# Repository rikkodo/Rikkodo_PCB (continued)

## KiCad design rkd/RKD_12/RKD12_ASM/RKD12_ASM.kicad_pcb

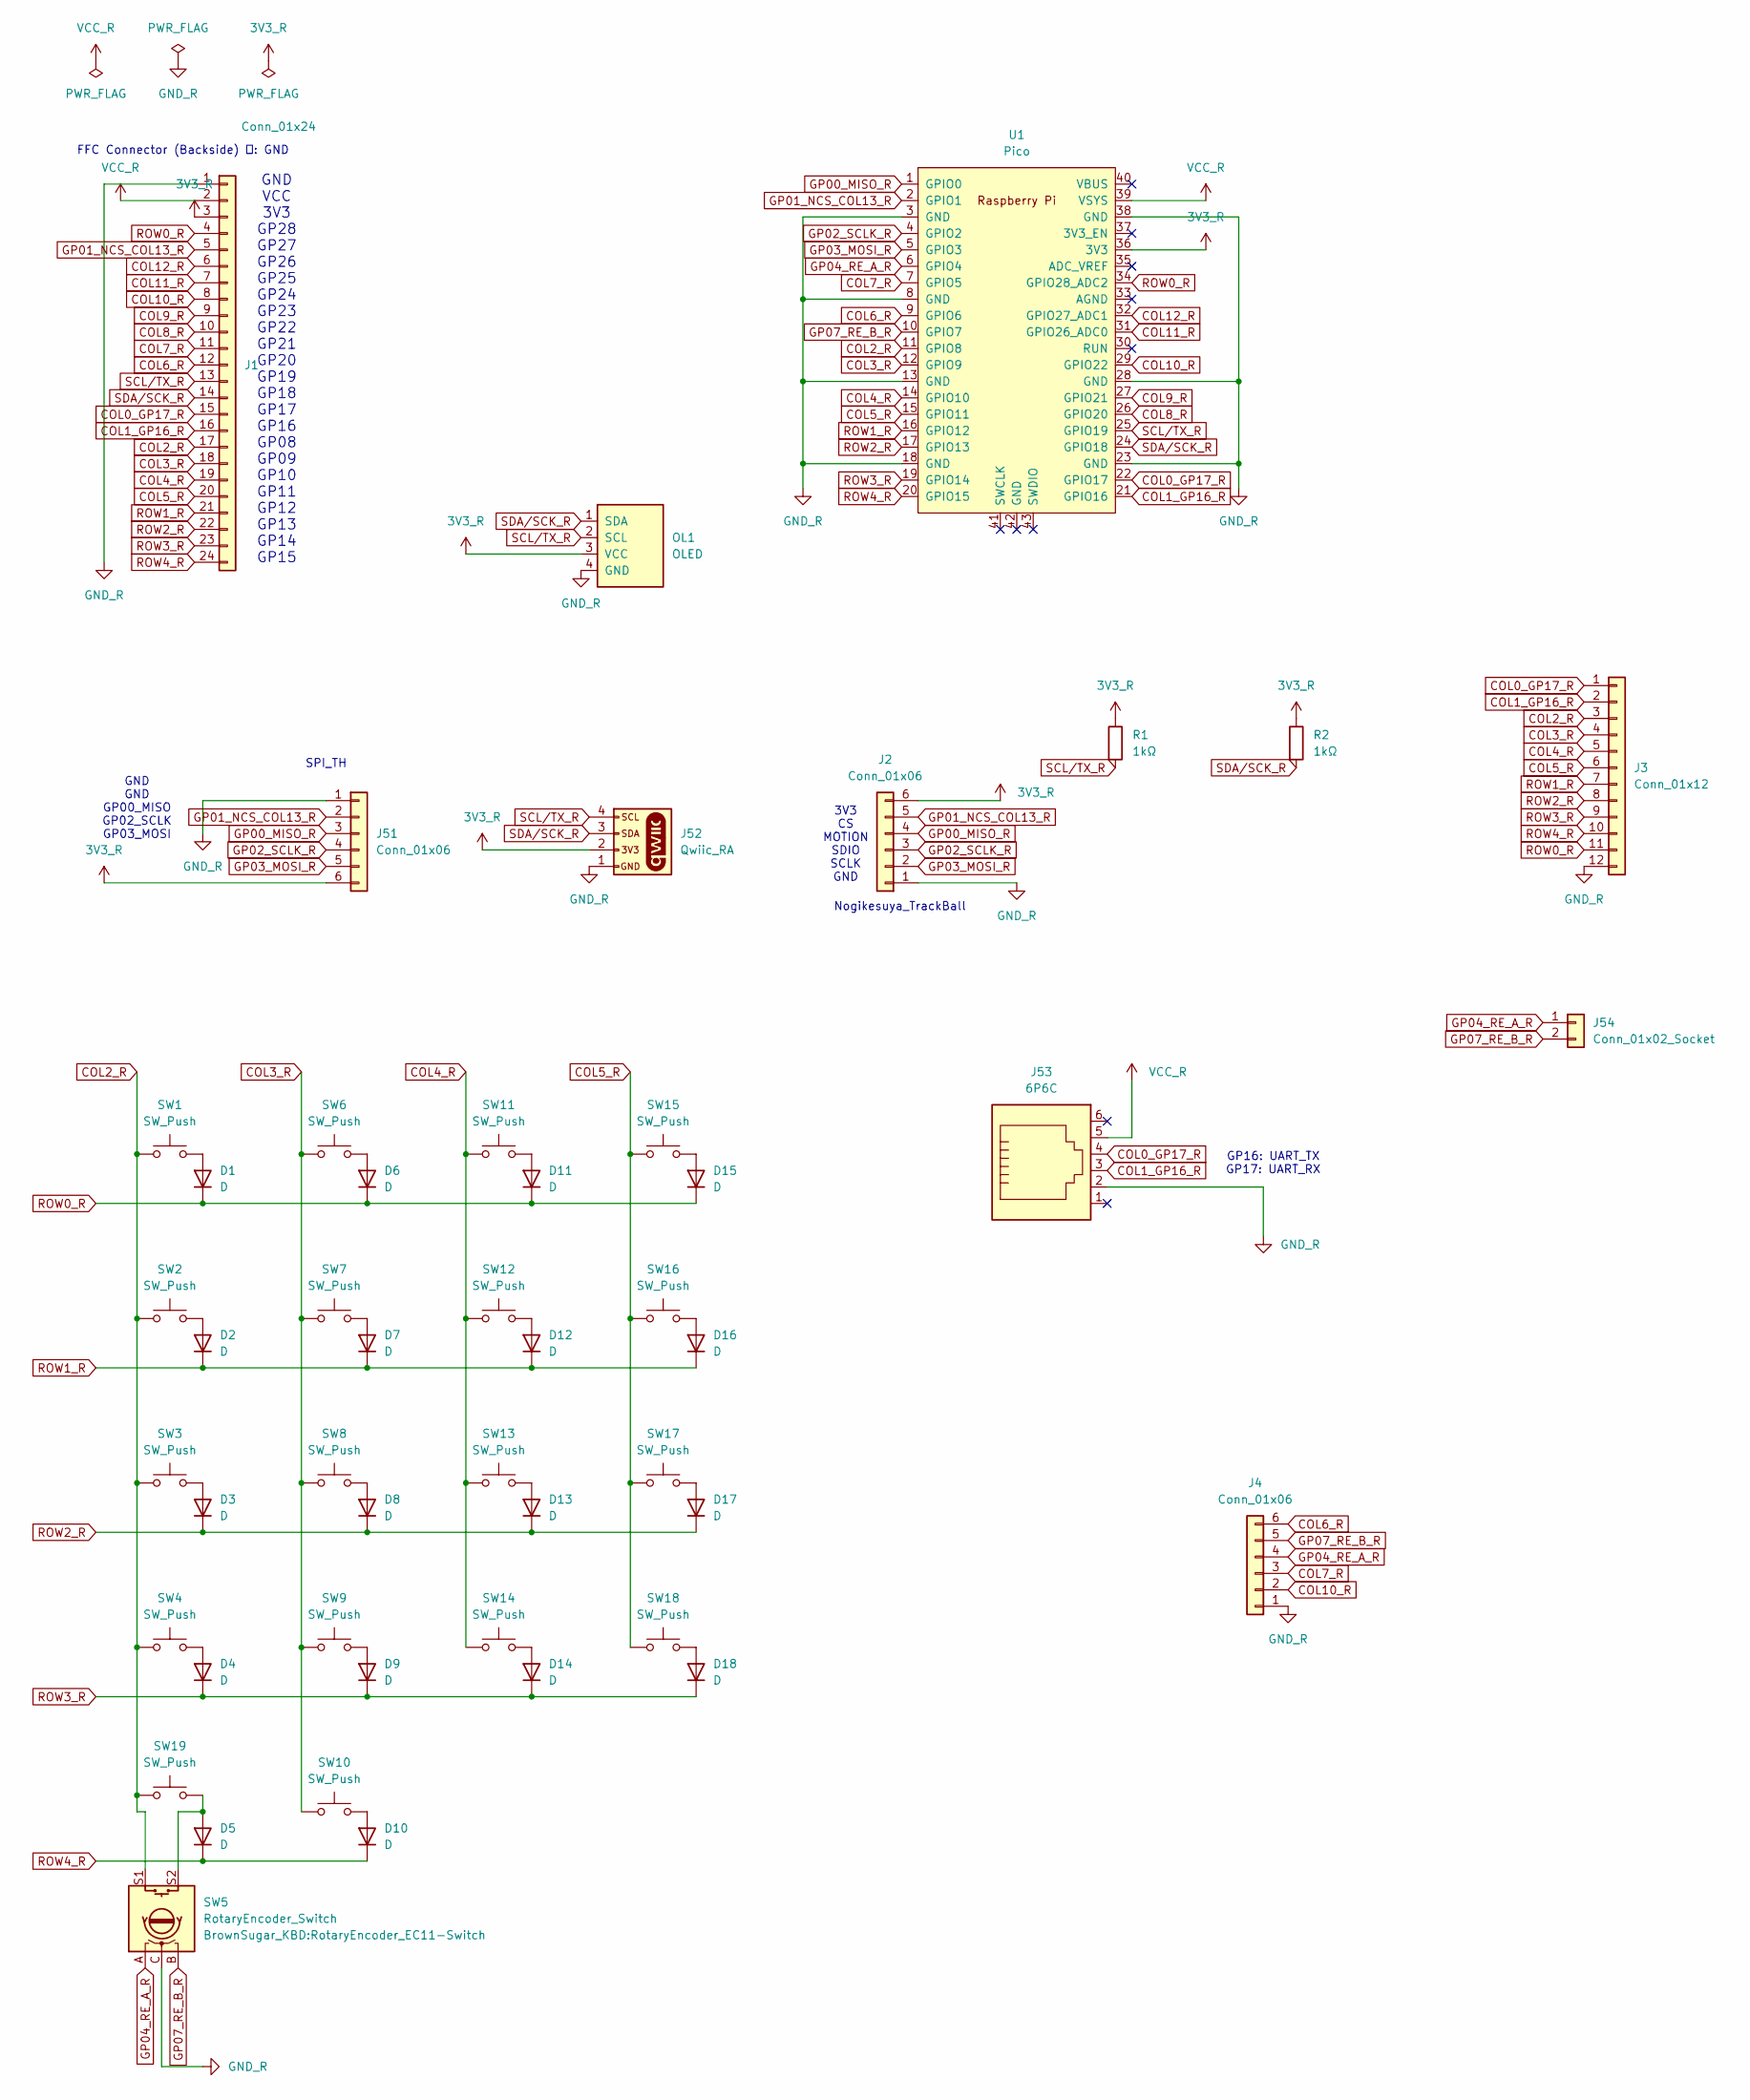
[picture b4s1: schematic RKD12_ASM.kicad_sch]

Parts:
D1, D2, D3, D4, D5, D6, D7, D8, D9, D10, D11, D12, D13, D14, D15, D16, D17, D18: D; Diode_SMD
J1: Conn_01x24; Hirose_FH12-24S-0.5SH_1x24-1MP_P0.50mm_Horizontal
J2, J4: Conn_01x06; Hirose_FH12-6S-0.5SH_1x06-1MP_P0.50mm_Horizontal
J3: Conn_01x12; Hirose_FH12-12S-0.5SH_1x12-1MP_P0.50mm_Horizontal
J51: Conn_01x06; PinHeader_1x06_P2.54mm_Horizontal
J52: Qwiic_RA; JST_SMD_1.0mm-4_Black
J53: 6P6C; RJ12_Amphenol_54601-x06_Horizontal
J54: Conn_01x02_Socket; PinHeader_1x02_P2.54mm_Vertical
OL1: OLED; OLED_center_display
R1, R2: 1kΩ; R_0603_1608Metric
SW1, SW2, SW3, SW4, SW6, SW7, SW8, SW9, SW10, SW11, SW12, SW13, SW14, SW15, SW16, SW17, SW18: SW_Push; rkd_Asm_ChocV1V2_Hotswap_1u_NM
SW5: RotaryEncoder_Switch; RotaryEncoder_EC11-Switch
SW19: SW_Push; ResetSW
U1: Pico; rkd_RPi_Pico_TH_NODBG

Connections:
3V3_R: J1.3, J2.6, J51.6, J52.2, OL1.3 (VCC), R1.1, R2.1, U1.36 (3V3)
COL0_GP17_R: J1.15, J3.1, J53.4, U1.22 (GPIO17)
COL1_GP16_R: J1.16, J3.2, J53.3, U1.21 (GPIO16)
COL2_R: J1.17, J3.3, SW1.2, SW2.2, SW3.2, SW4.2, SW5.S1, SW19.2, U1.11 (GPIO8)
COL3_R: J1.18, J3.4, SW6.2, SW7.2, SW8.2, SW9.2, SW10.2, U1.12 (GPIO9)
COL4_R: J1.19, J3.5, SW11.2, SW12.2, SW13.2, SW14.2, U1.14 (GPIO10)
COL5_R: J1.20, J3.6, SW15.2, SW16.2, SW17.2, SW18.2, U1.15 (GPIO11)
COL6_R: J1.12, J4.6, U1.9 (GPIO6)
COL7_R: J1.11, J4.3, U1.7 (GPIO5)
COL8_R: J1.10, U1.26 (GPIO20)
COL9_R: J1.9, U1.27 (GPIO21)
COL10_R: J1.8, J4.2, U1.29 (GPIO22)
COL11_R: J1.7, U1.31 (GPIO26_ADC0)
COL12_R: J1.6, U1.32 (GPIO27_ADC1)
GND_R: J1.1, J2.1, J3.12, J4.1, J51.1, J52.1, J53.2, OL1.4 (GND), SW5.C, U1.3 (GND), U1.8 (GND), U1.13 (GND), U1.18 (GND), U1.23 (GND), U1.28 (GND), U1.38 (GND)
GP00_MISO_R: J2.4, J51.3, U1.1 (GPIO0)
GP01_NCS_COL13_R: J1.5, J2.5, J51.2, U1.2 (GPIO1)
GP02_SCLK_R: J2.3, J51.4, U1.4 (GPIO2)
GP03_MOSI_R: J2.2, J51.5, U1.5 (GPIO3)
GP04_RE_A_R: J4.4, J54.1, SW5.A, U1.6 (GPIO4)
GP07_RE_B_R: J4.5, J54.2, SW5.B, U1.10 (GPIO7)
unnamed: D1.2 (A), SW1.1
unnamed: D2.2 (A), SW2.1
unnamed: D3.2 (A), SW3.1
unnamed: D4.2 (A), SW4.1
unnamed: D5.2 (A), SW5.S2, SW19.1
unnamed: D6.2 (A), SW6.1
unnamed: D7.2 (A), SW7.1
unnamed: D8.2 (A), SW8.1
unnamed: D9.2 (A), SW9.1
unnamed: D10.2 (A), SW10.1
unnamed: D11.2 (A), SW11.1
unnamed: D12.2 (A), SW12.1
unnamed: D13.2 (A), SW13.1
unnamed: D14.2 (A), SW14.1
unnamed: D15.2 (A), SW15.1
unnamed: D16.2 (A), SW16.1
unnamed: D17.2 (A), SW17.1
unnamed: D18.2 (A), SW18.1
ROW0_R: D1.1 (K), D6.1 (K), D11.1 (K), D15.1 (K), J1.4, J3.11, U1.34 (GPIO28_ADC2)
ROW1_R: D2.1 (K), D7.1 (K), D12.1 (K), D16.1 (K), J1.21, J3.7, U1.16 (GPIO12)
ROW2_R: D3.1 (K), D8.1 (K), D13.1 (K), D17.1 (K), J1.22, J3.8, U1.17 (GPIO13)
ROW3_R: D4.1 (K), D9.1 (K), D14.1 (K), D18.1 (K), J1.23, J3.9, U1.19 (GPIO14)
ROW4_R: D5.1 (K), D10.1 (K), J1.24, J3.10, U1.20 (GPIO15)
SCL/TX_R: J1.13, J52.4, OL1.2 (SCL), R1.2, U1.25 (GPIO19)
SDA/SCK_R: J1.14, J52.3, OL1.1 (SDA), R2.2, U1.24 (GPIO18)
VCC_R: J1.2, J53.5, U1.39 (VSYS)

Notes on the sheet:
Nogikesuya_TrackBall
3V3 CS MOTION SDIO SCLK GND
GND GND GP00_MISO GP02_SCLK GP03_MOSI
SPI_TH
GP16: UART_TX GP17: UART_RX
FFC Connector (Backside) １: GND
GND VCC 3V3 GP28 GP27 GP26 GP25 GP24 GP23 GP22 GP21 GP20 GP19 GP18 GP17 GP16 GP08 GP09 GP10 GP11 GP12 GP13 GP14 GP15

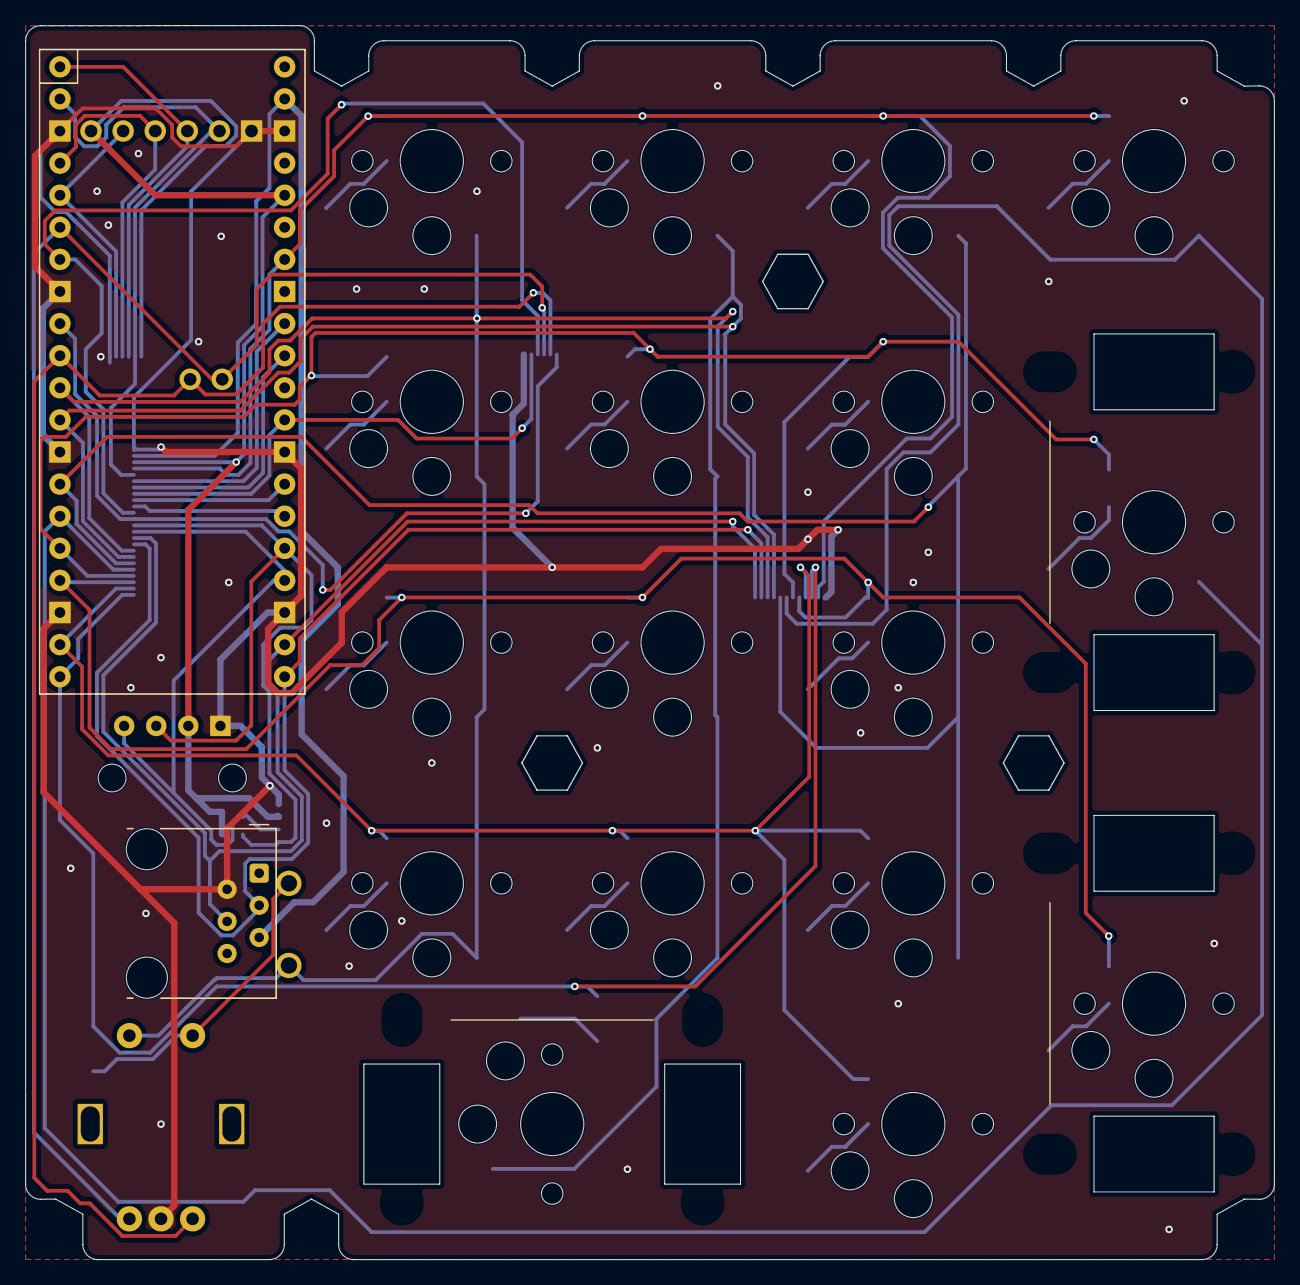
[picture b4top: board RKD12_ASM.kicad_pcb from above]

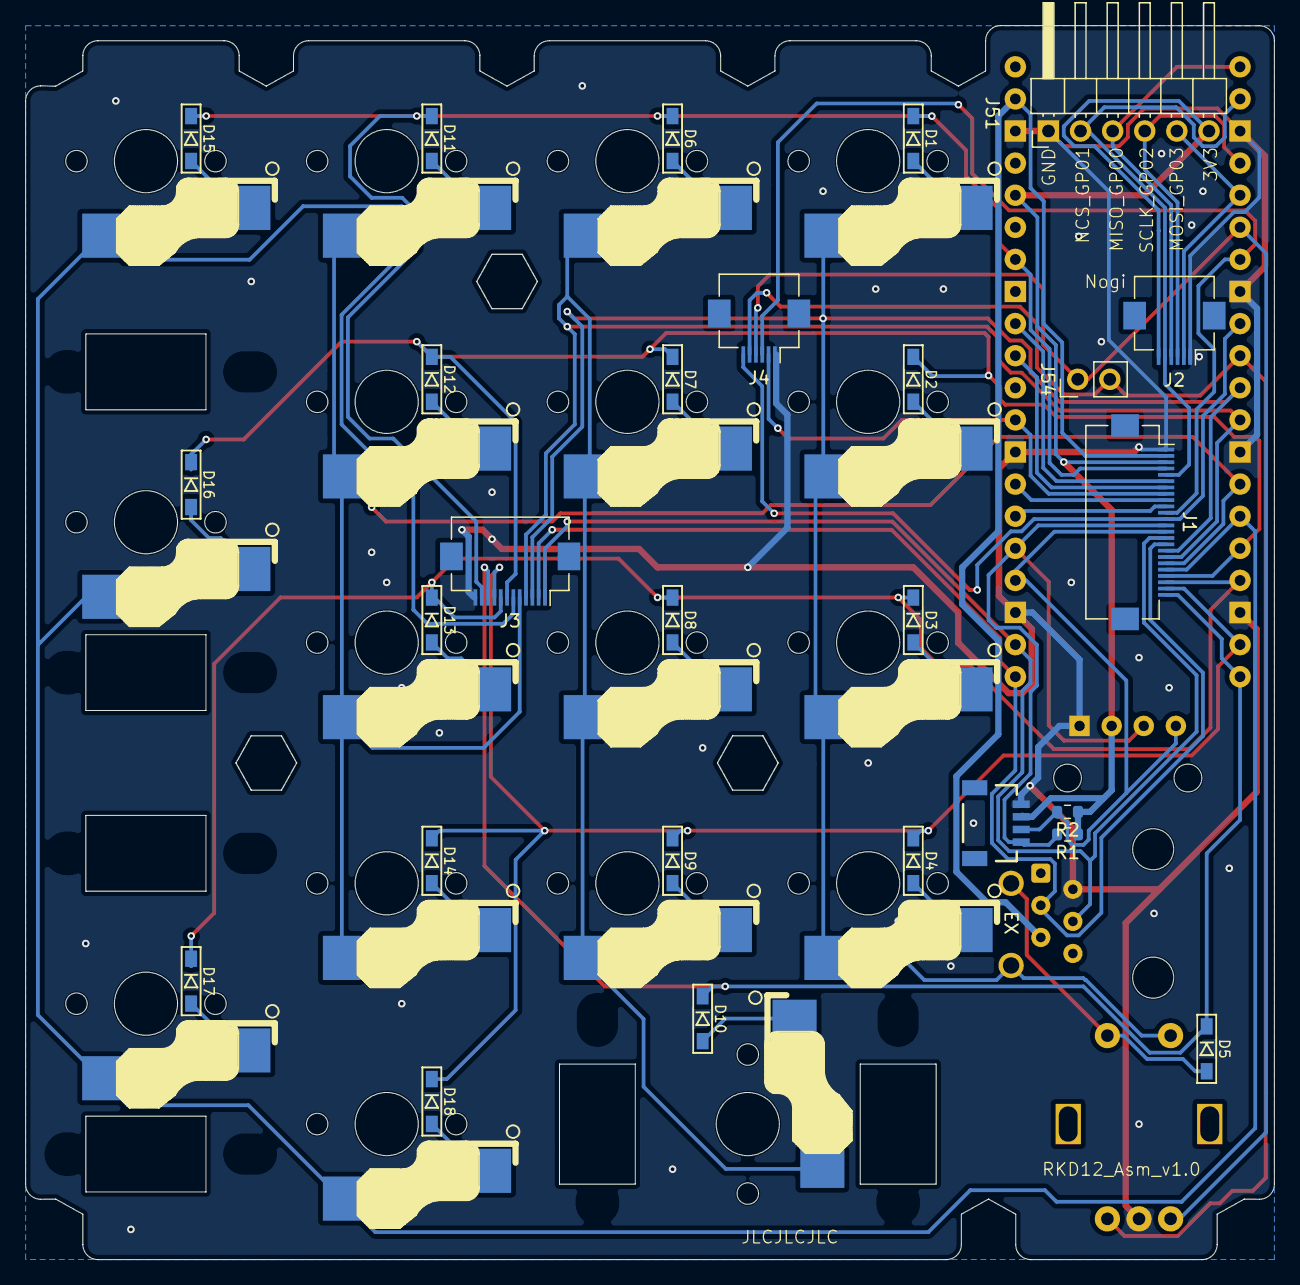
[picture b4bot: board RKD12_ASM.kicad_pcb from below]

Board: 2 copper layers, 98.8 x 97.6 mm, 56 parts (9 on the bottom side), 47 nets.

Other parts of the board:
Point1: Guard_Screw_Hall; rkd_Guard_Screw_Hall
Ref**: Val**; m2_Spacer_Hole_hex
Ref**#2, Ref**#3: Val**; m2_Spacer_Hole_hex
SW99, SW99#2, SW99#3: KEY_SWITCH; rkd_Asm_ChocV2_PCBMountStab_2uL

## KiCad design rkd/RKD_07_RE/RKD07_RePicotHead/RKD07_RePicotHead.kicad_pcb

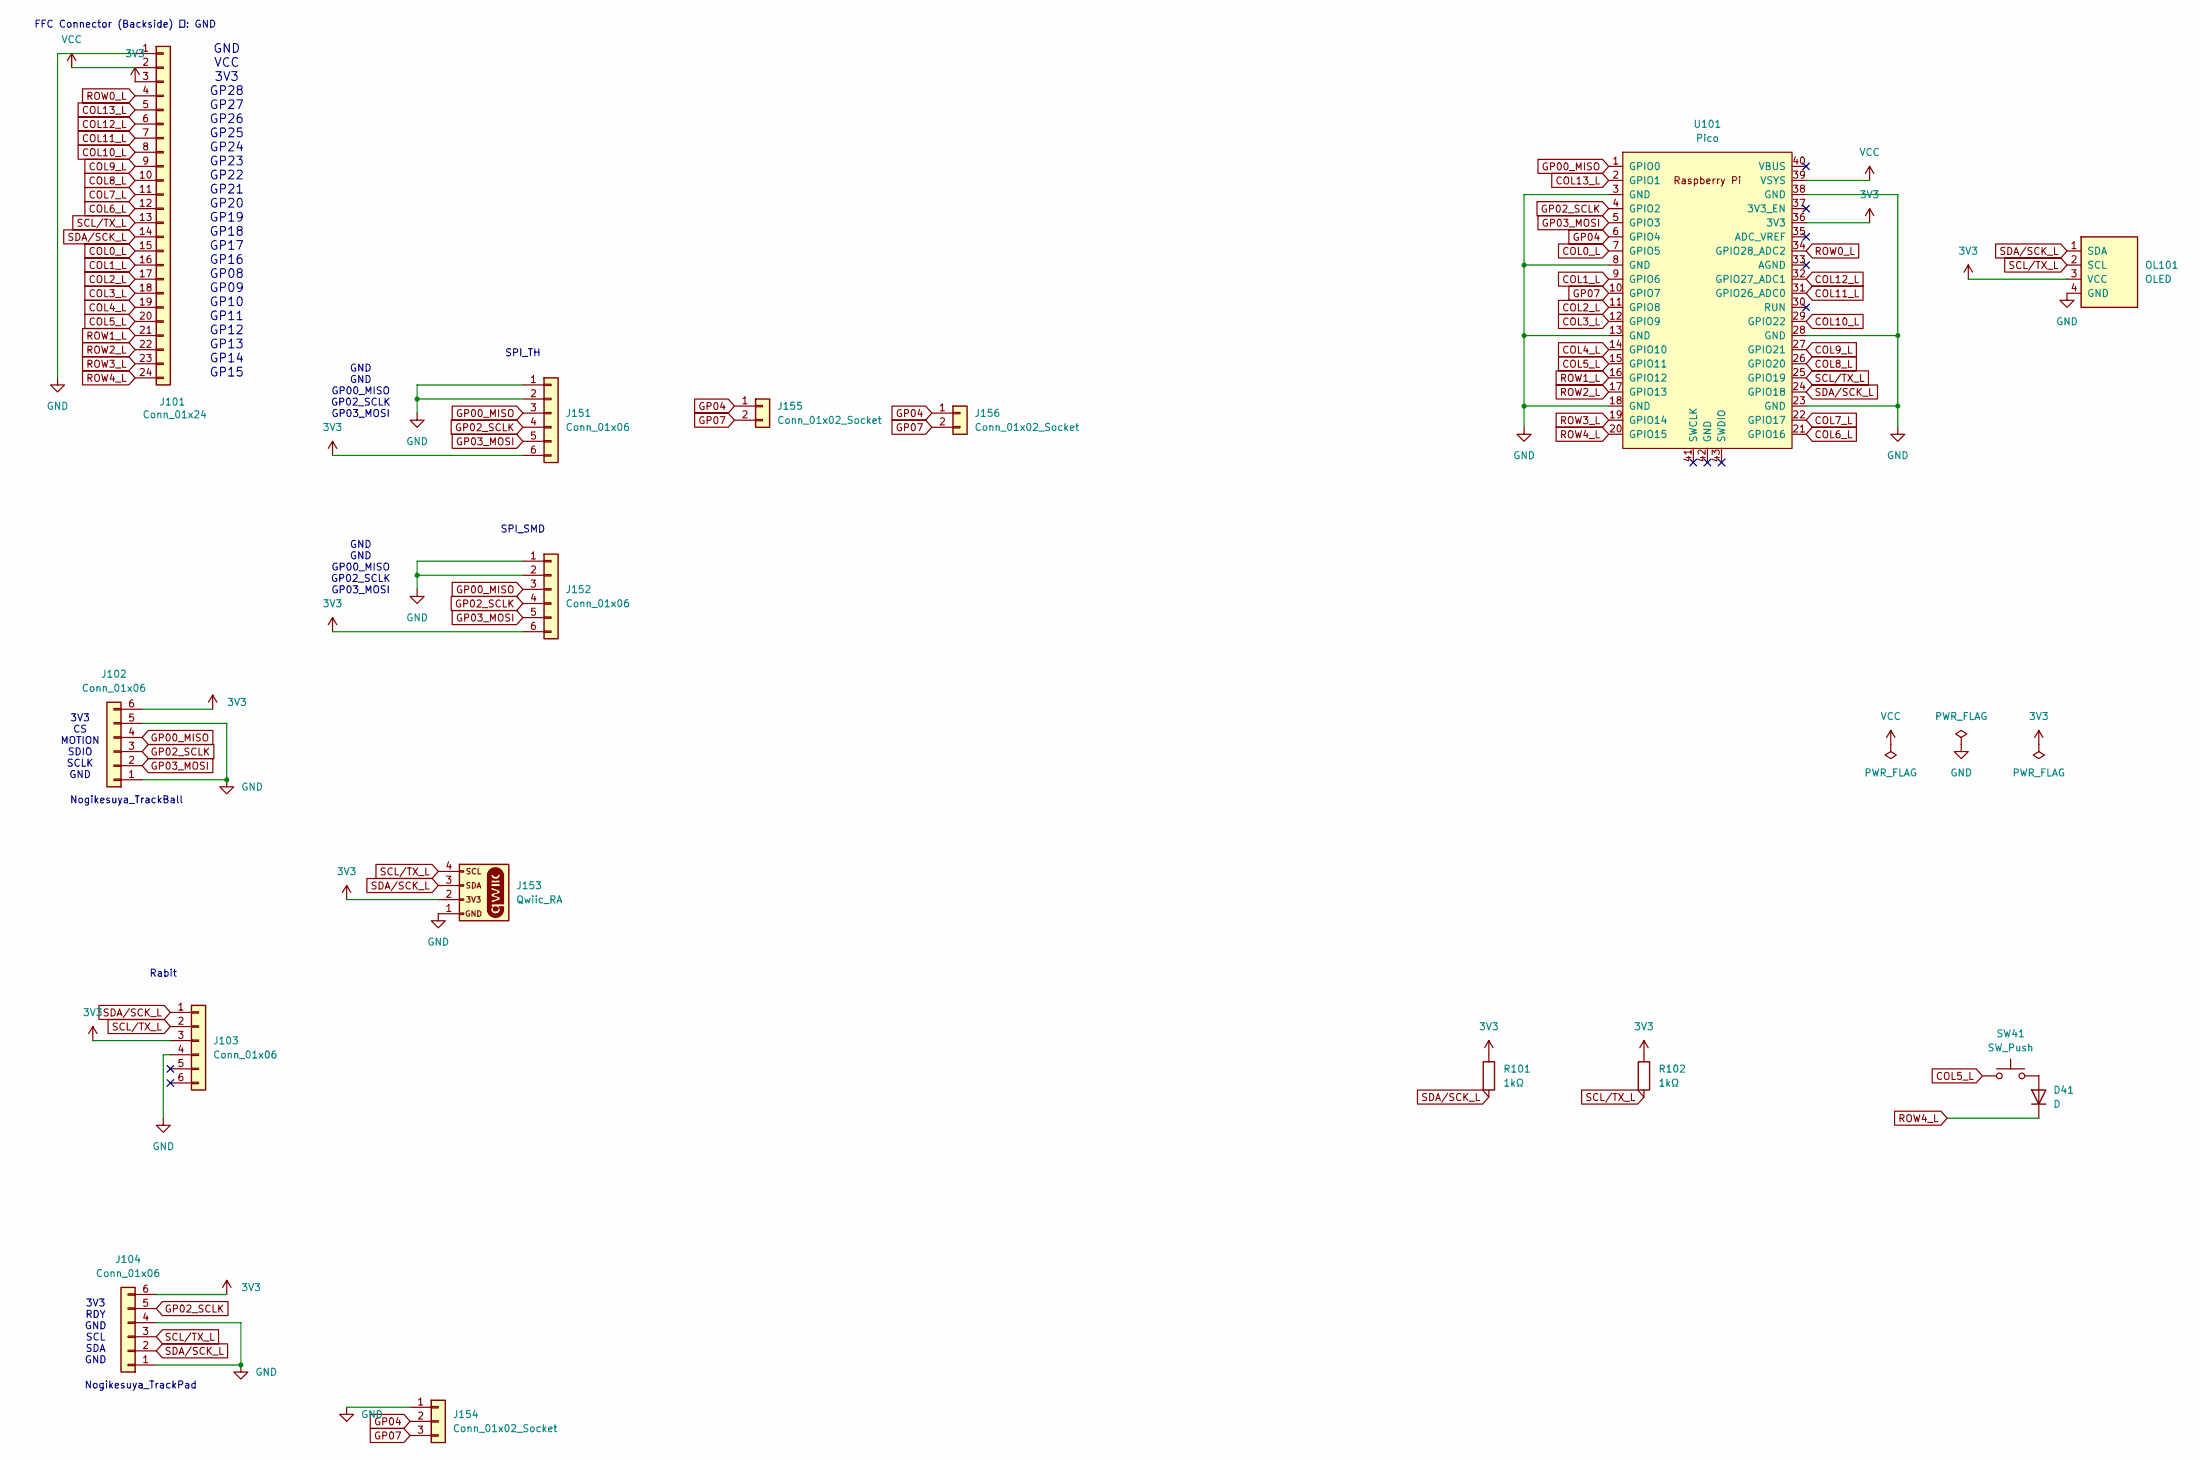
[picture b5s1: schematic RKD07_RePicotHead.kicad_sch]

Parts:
D41: D; Diode_SMD
J101: Conn_01x24; Hirose_FH12-24S-0.5SH_1x24-1MP_P0.50mm_Horizontal
J102, J103, J104: Conn_01x06; Hirose_FH12-6S-0.5SH_1x06-1MP_P0.50mm_Horizontal
J151: Conn_01x06; PinHeader_1x06_P2.54mm_Horizontal
J152: Conn_01x06; Harwin_M20-89006xx_1x06_P2.54mm_Horizontal
J153: Qwiic_RA; JST_SMD_1.0mm-4_Black
J154: Conn_01x02_Socket; Harwin_M20-89003xx_1x03_P2.54mm_Horizontal
J155, J156: Conn_01x02_Socket; PinHeader_1x02_P2.54mm_Horizontal
OL101: OLED; OLED_center_display
R101, R102: 1kΩ; R_0603_1608Metric
SW41: SW_Push; rkd_Asm_ChocV1V2_Hotswap_1u
U101: Pico; rkd_RPi_Pico_TH_NODBG

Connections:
3V3: J101.3, J102.6, J103.3, J104.6, J151.6, J152.6, J153.2, OL101.3 (VCC), R101.1, R102.1, U101.36 (3V3)
COL0_L: J101.15, U101.7 (GPIO5)
COL1_L: J101.16, U101.9 (GPIO6)
COL2_L: J101.17, U101.11 (GPIO8)
COL3_L: J101.18, U101.12 (GPIO9)
COL4_L: J101.19, U101.14 (GPIO10)
COL5_L: J101.20, SW41.2, U101.15 (GPIO11)
COL6_L: J101.12, U101.21 (GPIO16)
COL7_L: J101.11, U101.22 (GPIO17)
COL8_L: J101.10, U101.26 (GPIO20)
COL9_L: J101.9, U101.27 (GPIO21)
COL10_L: J101.8, U101.29 (GPIO22)
COL11_L: J101.7, U101.31 (GPIO26_ADC0)
COL12_L: J101.6, U101.32 (GPIO27_ADC1)
COL13_L: J101.5, U101.2 (GPIO1)
GND: J101.1, J102.1, J102.5, J103.4, J104.1, J104.4, J151.1, J151.2, J152.1, J152.2, J153.1, J154.1, OL101.4 (GND), U101.3 (GND), U101.8 (GND), U101.13 (GND), U101.18 (GND), U101.23 (GND), U101.28 (GND), U101.38 (GND)
GP00_MISO: J102.4, J151.3, J152.3, U101.1 (GPIO0)
GP02_SCLK: J102.3, J104.5, J151.4, J152.4, U101.4 (GPIO2)
GP03_MOSI: J102.2, J151.5, J152.5, U101.5 (GPIO3)
GP04: J154.2, J155.1, J156.1, U101.6 (GPIO4)
GP07: J154.3, J155.2, J156.2, U101.10 (GPIO7)
unnamed: D41.2 (A), SW41.1
ROW0_L: J101.4, U101.34 (GPIO28_ADC2)
ROW1_L: J101.21, U101.16 (GPIO12)
ROW2_L: J101.22, U101.17 (GPIO13)
ROW3_L: J101.23, U101.19 (GPIO14)
ROW4_L: D41.1 (K), J101.24, U101.20 (GPIO15)
SCL/TX_L: J101.13, J103.2, J104.3, J153.4, OL101.2 (SCL), R102.2, U101.25 (GPIO19)
SDA/SCK_L: J101.14, J103.1, J104.2, J153.3, OL101.1 (SDA), R101.2, U101.24 (GPIO18)
VCC: J101.2, U101.39 (VSYS)

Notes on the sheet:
Nogikesuya_TrackPad
SPI_SMD
GND GND GP00_MISO GP02_SCLK GP03_MOSI
Rabit
3V3 RDY GND SCL SDA GND
SPI_TH
Nogikesuya_TrackBall
3V3 CS MOTION SDIO SCLK GND
FFC Connector (Backside) １: GND
GND VCC 3V3 GP28 GP27 GP26 GP25 GP24 GP23 GP22 GP21 GP20 GP19 GP18 GP17 GP16 GP08 GP09 GP10 GP11 GP12 GP13 GP14 GP15

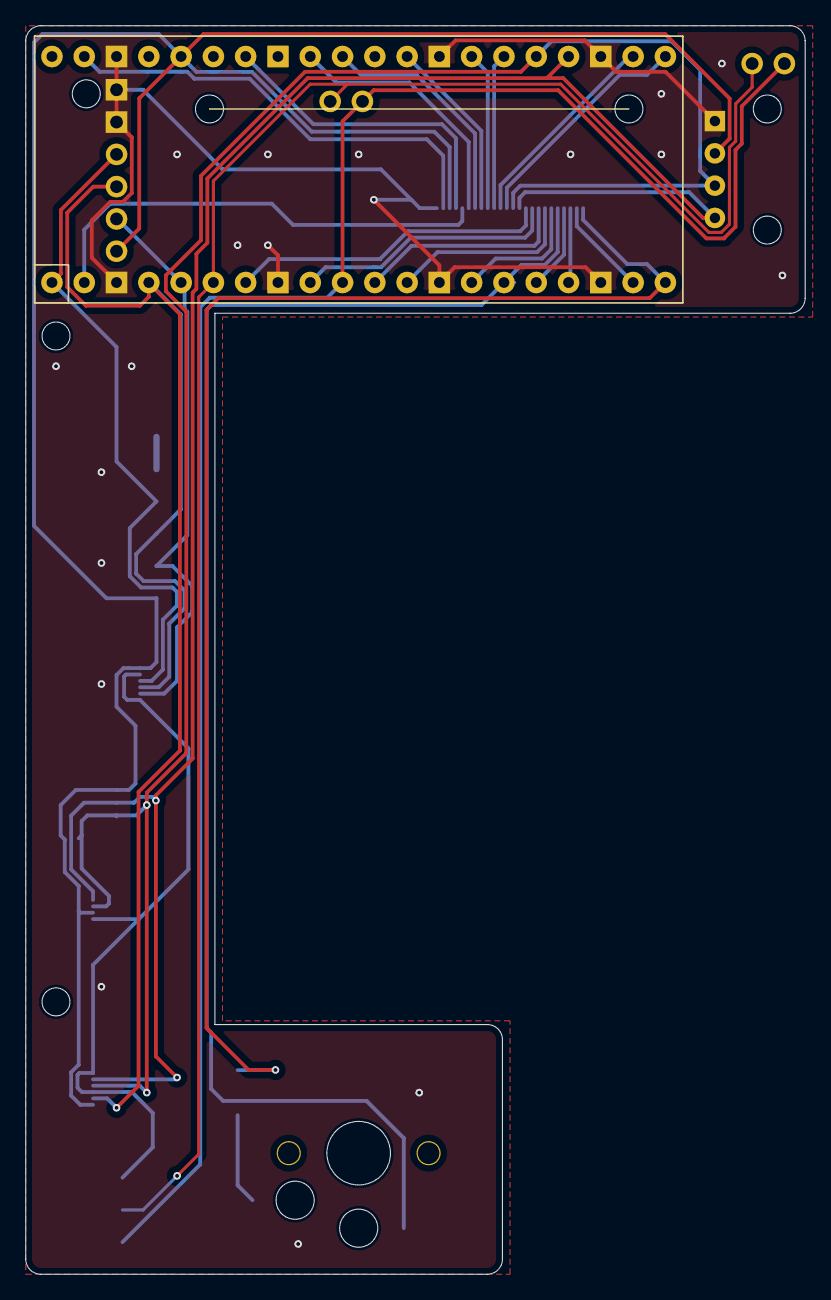
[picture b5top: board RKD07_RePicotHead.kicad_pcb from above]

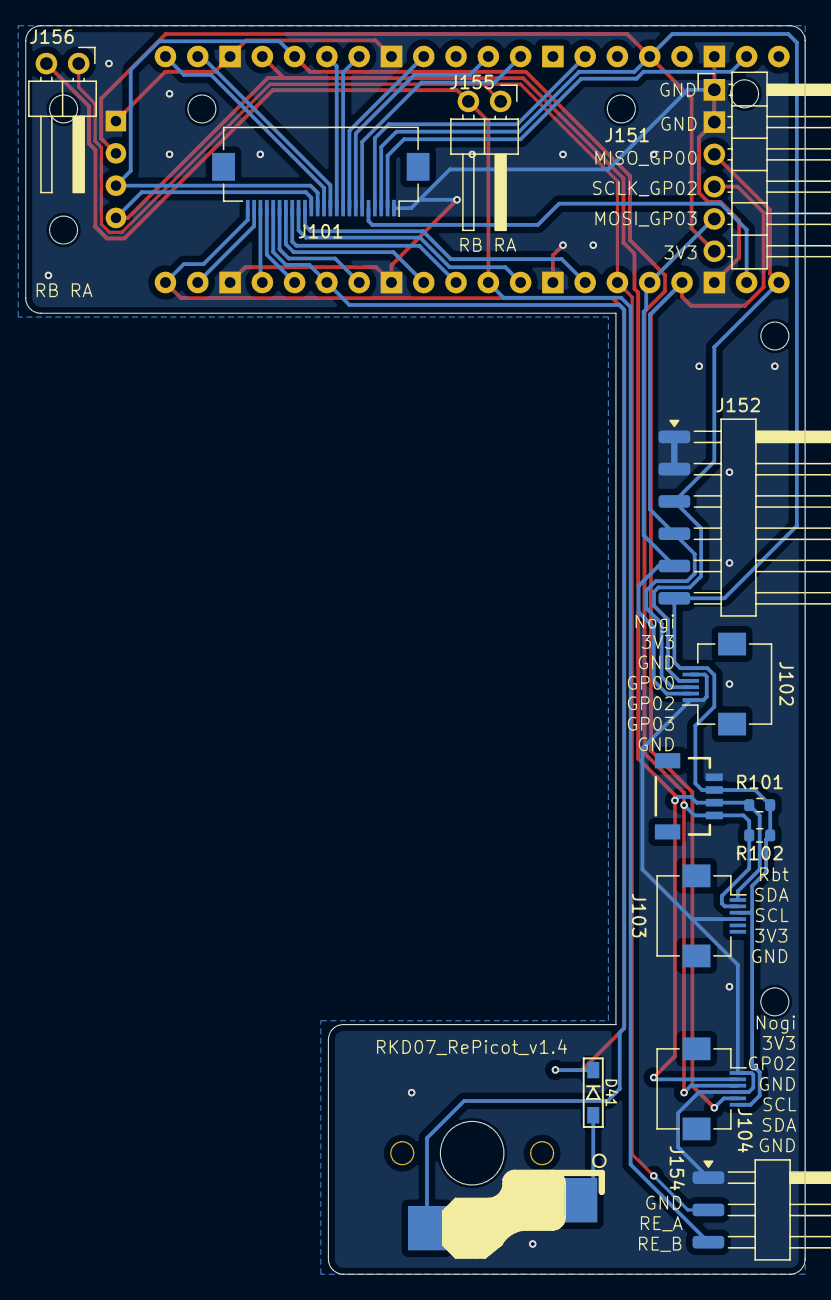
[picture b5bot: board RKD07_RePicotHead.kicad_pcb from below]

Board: 2 copper layers, 61.3 x 98.2 mm, 22 parts (12 on the bottom side), 30 nets.

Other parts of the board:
Ref**: Val**; m2_Screw_Hole
Ref**#2, Ref**#3, Ref**#4, Ref**#5: Val**; m2_Screw_Hole
UnifiedW**: rkd_unified_wid_BTM

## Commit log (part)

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2025-01-02 ネジ穴位置の誤り修正
2025-01-02 ダイオードが微妙にずれていたので修正
2025-01-03 ScrewHall追加
2025-01-03 部品追加
2025-01-03 要修正点を記載
2025-01-03 初回登録
2025-01-03 Ball版を削除
2025-01-03 v1.5
2025-01-04 OLEDを追加
2025-01-04 配置変更
2025-01-05 アクスタ用の穴
2025-01-05 RKD03初回登録
2025-01-05 LEDの誤り修正1.01
2025-01-05 ツールの更新
2025-01-05 toolを修正
2025-01-06 README更新
2025-01-06 I2Cの入力を3.3Vに修正
2025-01-06 ぼつ追加
2025-01-06 基板を正しく支えられない問題を記載
2025-01-06 RKD02 Bottom, Topを作成
2025-01-06 ガーバー作成
2025-01-07 RKD02_配線の調整
2025-01-07 via用のtool追加
2025-01-08 RKD03V2作成中
2025-01-08 バージョン表記を修正
2025-01-08 共通部品のRename
2025-01-09 フットプリント追加
2025-01-09 スイッチフットプリントをChocV2に修正
2025-01-09 RKD03 試行錯誤中
2025-01-09 RKD02 ChocV2に修正中
2025-01-10 RKD01_DRC
2025-01-10 使用しないfootprintを削除
2025-01-10 RKD01 右 ファイル名変更もれ対応 SPの削除
2025-01-10 RKD02 Asm 微修正
2025-01-11 RKD03_手直し
2025-01-11 MDの警告を除去
2025-01-11 RKD02 配線を調整
2025-01-11 RKD02 modify
2025-01-11 非ホットスワップFootPrint追加
2025-01-11 Chocフットプリントを追加
2025-01-11 名前変更
2025-01-11 RKD02 V1V2両用版試作
2025-01-11 ネジ穴位置変更
2025-01-11 RKD03 LED微調整
2025-01-12 RKD02 回路図側もV1V2に修正
2025-01-12 v1v2に修正
2025-01-12 TH,V2を没行き
2025-01-12 RKD02 V1V2に修正
2025-01-12 RKD03 V1V2に修正
2025-01-12 RKD02 配線調整
2025-01-12 RKD02 角の丸みを追加
2025-01-12 RKD02 角丸調整2
    Guardの角は1/16を採用
2025-01-13 RKD02_支柱穴を追加
2025-01-15 フットプリント Gateron Lowprofile Stabilizer検証
2025-01-15 備忘追加
2025-01-15 フットプリント誤り修正
2025-01-15 RKD03 新フットプリントの検証
2025-01-15 holeの変更
2025-01-17 入力の問題点を追記
2025-01-17 RKD02 フットプリントのエラー調整
2025-01-17 RKD03 Gateron/Chocモデルを追加
2025-01-17 RKD03 RE用の穴を修正
2025-01-17 RKD03 AddName
2025-01-17 RKD03 V1Top 仮登録
2025-01-17 ChocV2 メイン穴径を5mmに
2025-01-17 ChocV2のステム径に合わせて修正
2025-01-19 RKD03 プロット
2025-01-19 微妙なフットプリントを削除
2025-01-19 Cherry+Choc追加
2025-01-19 V1.2
2025-01-20 スタンド用穴をわずかに短く
2025-01-20 RKD03V1 穴サイズを狭く
2025-01-20 plot
2025-01-21 README追加
2025-01-23 新FootPrint追加
2025-01-23 PlayGround追加
2025-01-23 AzFoot更新
2025-01-23 RKDV3 見直し
2025-01-23 コンスルー対応
2025-01-23 OLEDガード作成
2025-01-23 RKD03修正
2025-01-23 rkd02修正
2025-01-24 Rename
2025-01-24 ChocV2 Stab Test
2025-01-24 Cinderella型構築
2025-01-26 CC2U作成
2025-01-26 RKD03 V2新規
2025-01-26 RKD03 V1V2 Top新規
2025-01-26 RKD03 LED位置を調整
2025-01-26 ChocV2スタビの可能性
2025-01-27 Refference追加
2025-01-27 RKD03 2u修正
2025-01-27 OLEDGuard OLED用窓追加
2025-01-27 RKD02 footprint修正
2025-01-29 RKD02 キー配置修正
2025-01-29 RKD03 穴の追加
2025-01-29 Common 微細部品追加
2025-01-29 RKD03 部品修正
2025-01-29 部品誤り修正
2025-02-02 FootPrint 2uWシリーズ追加
2025-02-02 RKD03 2uWシリーズ適用
2025-02-02 RKD02 2uWシリーズ適用
2025-02-02 FootPrint メモ追加
2025-02-02 AzFoot Qwiic追加
2025-02-02 RKD03 GND解放ミス
2025-02-09 02, 03 表面側にQwiicを追加
2025-02-09 CinderellaUpdate
2025-02-10 ChangeHoleSize
2025-02-13 RKD02 RE追加
2025-02-13 AzFootQwiicOnly初回
2025-02-13 大量のタクトスイッチ
2025-02-14 picot5400予約
2025-02-14 MyFootPrint
2025-02-15 Unified追加
2025-02-15 RKD02 Unified想定
2025-02-15 RKD02 新型Top
2025-02-15 RKD02 Picokt調整
2025-02-15 TopをRename
2025-02-16 RKD02 Revision
2025-02-16 UpdateFootPrint
2025-02-16 RKD02_AddScrewHoles
2025-02-16 RKD03_EraseFoot
2025-02-16 Common UpdateFootPrint
2025-02-16 Order用に面付け
2025-02-16 Order用の内容を削減
2025-02-16 RKD02_チップ修正
2025-02-16 breakoutboard作成
2025-02-16 RKD03 Point箇所修正もれ
2025-02-16 Picot用テンプレート初回作成
2025-02-16 tool利用
2025-02-16 RKD04 ASM初回登録
2025-02-17 RKD02 線位置等調整
2025-02-17 RKD04 考慮漏れ修正
2025-02-17 RKD04対応
2025-02-18 FP PointHoleを広くした
2025-02-18 RKD02 大量に調整
2025-02-18 04対応
2025-02-18 せんを太くした
2025-02-18 SekiBall追加
2025-02-18 ワッシャー追加
2025-02-20 SekiBall シルクプリントの除去
2025-02-20 SekiBall用のfoot追加
2025-02-20 Point用の穴を一ます大きくした
2025-02-20 ORDER 不要パーツ削除
2025-02-20 RKD03_SekiConn
2025-02-20 RKD04 AddTop
2025-02-20 RKD02 見直し
2025-02-20 RKD02 結線を変更
2025-02-20 RKD05 初回登録
2025-02-22 RKD02 _I2CコネクタをSPI使える組み合わせに変更
2025-02-22 RKD03 I2CコネクタをSPI使える組み合わせに変更
2025-02-22 RKD04_width0.2配線を0.25に修正
2025-02-22 RKD05_width0.2配線を0.25に修正
2025-02-22 大きめのロゴ追加
2025-02-22 RKD05 RE用PIN追加
2025-02-22 RKD02 05用の修正
2025-02-22 RKD05 ロゴの誤りを修正
2025-02-23 RKD02_コネクタ配置を変更
2025-02-23 RKD02 6Pin追加
2025-02-23 FootPrint Rpi_THのコートヤードを削除
2025-02-23 RKD05 GNDテキスト追加
2025-02-23 RKD02 GNDテキスト追加
2025-02-23 線の追加・名前の表示など
2025-02-23 RKD02 Tocip用穴追加
2025-02-23 RKD_Topic 新規追加
2025-02-24 Commonよくわからん
2025-02-24 SekiFoot新規作成
2025-02-24 RKD05 PinAssign変更’
2025-02-24 RKD03 SekiFoot位置変更
2025-02-24 Order1 調整
2025-02-24 Order2 新規作成
2025-02-24 RKD02 TOPロゴ入れ追加
2025-02-24 Aパーツ、Bパーツ作成
2025-02-24 RKD05接続名変更
2025-02-24 RKD06 初回登録
2025-02-25 RKD02 不要なCOL14を削除
2025-02-25 RKD03 QWIIC用の逃げ穴を作成
2025-02-25 RKD03シルク調整
2025-02-25 RKD06 QWIIC追加
2025-02-25 RKD06 Functionキー列を1/8u上に
2025-02-25 RKD06
2025-02-26 ChocV2FootPrint見直し
2025-02-26 RKD03 FootPrint見直しに伴い修正
2025-02-26 RKD06 Bottom(Botsu)
2025-02-26 RKD06更新
2025-02-26 RKD06 配線途中
2025-02-26 RKD06 配線 途中
2025-02-28 FootPrint 半田付けに余裕を
2025-02-28 RKD06コア更新
2025-02-28 RKD03 半田付けエリア延長
2025-02-28 RKD03 TOP修正
2025-02-28 ミス修正
2025-02-28 LED穴作成
2025-02-28 TOP作成
2025-02-28 RKD-6修正
2025-03-01 穴空けようフットプリントに回路図にない属性を付与
2025-03-01 LED位置調整
2025-03-01 02バージョンアップ対応
2025-03-01 ORDER バージョンアップ対応
2025-03-01 05 バージョンアップ対応
2025-03-01 3,4 バージョンアップ対応
2025-03-01 6バージョンアップ対応
2025-03-01 06 配線
2025-03-01 出力先パスを設定
2025-03-02 ORDER REMAKE
2025-03-02 RKD04 補正
2025-03-02 update for order
2025-03-02 スタビ穴追加
2025-03-02 コネクタ位置変更
2025-03-02 04 KARI
2025-03-03 05 Remake
2025-03-03 06 for PCBA
2025-03-03 3V3と3V3ENの誤り修正
2025-03-16 06 BottomSimple作成
2025-03-20 定義変更
2025-03-20 07_初回登録
2025-03-22 RKD07 一時保存
2025-03-23 RePicot初回
2025-03-23 RKD03 FFP調整
2025-03-23 RePicot 更新
2025-03-23 RD07配線
2025-03-23 部品更新
2025-03-23 07 Modify
2025-03-23 07 さらに調整
2025-03-24 Point関係修正
2025-03-24 TRRS追加
2025-03-24 07Geek追加
2025-03-24 07 I2C配線見直し
2025-03-24 07 Top調整
2025-03-25 ChocV2スタビ編集
2025-03-25 07 部品１微調整
2025-03-25 穴一など修正
2025-03-25 BOTSU
2025-03-25 07 Pointingデバイス用スペースの見直し
2025-03-25 ネジ穴見直し
2025-03-25 07 I2C抵抗追加
2025-03-26 07 ワイヤ調整
2025-03-26 QWICC位置など調整
2025-03-28 LEDむき訂正
2025-03-28 OLED追加
2025-04-18 Modify for SekiBall
2025-05-01 RKD07 調整
2025-05-01 07AsmBuild First Commit
2025-05-03 旧Asmをボツに
2025-05-03 上幅を調整
2025-05-03 RePicotに伴う修正
2025-05-04 07 Release調整
2025-05-04 07 Release調整2
2025-05-04 07 Release調整3
2025-05-04 RePicotの修正
2025-05-04 CSをGND固定
2025-05-04 I2Cを色々追加
2025-05-05 07 I2Cを整理
2025-05-05 ADD Decoration
2025-05-05 Patternを独立
2025-05-05 Asanoha追加
2025-05-05 Asanoha
2025-05-05 Kicad Update AzFootQ
2025-05-18 Top修正
2025-05-18 TopV2
2025-05-18 Update Logo
2025-05-19 塗り直し
2025-05-19 Add Hole
2025-05-26 modify rkd07
2025-06-01 RKD07 v1.2
2025-06-02 Erratta
2025-06-04 Modify Tag
2025-06-09 Modify7.2
2025-06-10 Modify 7.2
2025-06-11 RePicot微調整
2025-06-11 ReMecab初回
2025-06-12 07 Rebuild
2025-06-13 stabilizer変更
2025-06-13 add mekabu
2025-06-15 add qwiic
2025-06-15 revision
2025-06-16 不要部品の除去
2025-06-16 Update Remecab
2025-06-16 釣天井システム新規作成
2025-06-16 TuritenRebuild
2025-06-16 釣天井更新
2025-06-16 穴周りを変更
2025-06-18 ReMecabu
2025-06-19 add_sumifoot
2025-06-20 RKD08 Meishi
2025-06-21 Redesign remecab
2025-06-22 edit meishi
2025-06-23 add 10
2025-06-24 30諦め
2025-06-24 30Revenge
2025-06-24 MOVE_30
2025-07-06 Update for sumi
2025-07-08 modify
2025-07-08 07PMW3360
2025-07-09 Pos修正
2025-07-12 Reシリーズ用穴追加
2025-07-13 RemakeRepicot
2025-07-13 modiry
2025-07-16 空白部に穴あけ
2025-07-28 plate用の穴追加
2025-07-28 RePicot修正
2025-08-03 Add NogikesuTrackpad
2025-08-03 order.
2025-08-05 11 first commit
2025-08-22 RePicot変更
2025-08-27 simplifi
2025-08-27 save
2025-08-31 RJ9搭載
2025-08-31 move to RE
2025-08-31 move re
2025-08-31 add Split
2025-09-15 ModifyDots
2025-09-15 add rj9 hole
2025-09-21 SplitR
2025-09-21 Add SplitL
2025-09-23 RePicotUpdate
2025-09-24 １2 first commit
2025-09-26 Combine
2025-09-30 Order1
2025-10-15 AddREOnLeft
2025-10-15 Error
2025-10-15 ZWER
2025-10-20 modify holes
2025-10-29 ZWEI_TOP/BOTTOM
2025-11-03 modify wire
2025-11-09 AddGuard
2025-11-12 抜け漏れ修正
2026-01-03 micro first commit
2026-02-08 EraseBimyo
2026-02-11 move
2026-02-22 配線もれ
2026-02-23 new generation
2026-05-03 add footprint Chocv2 only
2026-05-03 apply kicad update
2026-05-03 update trial
2026-05-03 remove
2026-05-03 trialam first commit
2026-05-04 update hole
2026-05-05 マウスセンサ部品
2026-05-05 miniシリーズのネジ穴追加
2026-05-05 add mini ortho top
2026-05-08 ポカよけ追加
